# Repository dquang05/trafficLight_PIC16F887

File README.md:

# Traffic Light Controller with PIC16F887

A embedded systems project that implements a 2-road traffic light controller on **PIC16F887**, with a **Python Tkinter desktop UI** for monitoring and control over UART. The project focuses on firmware development, peripheral integration, timer-based state control, and PC-side visualization.

## Features

- PIC16F887-based traffic light controller firmware
- 3 operating modes: **AUTO**, **MANUAL**, and **FLASHING**
- UART-based communication between the microcontroller and desktop UI
- Python Tkinter interface for live traffic light visualization
- I2C LCD for mode display on the hardware side
- Button control and serial command control support

## Operating Modes

### AUTO
Runs the normal traffic cycle automatically using timer-based state transitions. The UI displays countdown values for both roads.

### MANUAL
Allows the user to manually select which road gets the green light from the desktop UI.

### FLASHING
Puts the system into a caution mode where the yellow lights blink.

## How It Works

The PIC firmware handles the traffic light state machine, button input, UART command processing, and LCD updates. A timer interrupt is used for timekeeping, while the main loop updates the current mode and periodically sends system state data to the PC.

The desktop UI connects through a serial port, sends commands, and visualizes the current traffic light states in real time.

## Controls

Supported serial/UI commands:

- `A` → AUTO
- `N` → MANUAL
- `F` → FLASHING
- `M` → NEXT MODE
- `R1` → Road 1 Go
- `R2` → Road 2 Go

## How to Use

1. Build and flash the firmware to the PIC16F887.
2. Connect the board to the PC through UART.
3. Run the Python UI.
4. Select the correct COM port and baud rate, then press **Connect**.
5. Use the UI buttons to switch modes and control the intersection.

## Wiring Notes

- `RC3` → I2C SCL
- `RC4` → I2C SDA
- `RB0`, `RB1`, `RB2` → push buttons
- UART baud rate in the current setup: **9600**

## Fault notes
- This is a small project, i do not optimal it for fault tolerance, so there are some faults in the code, such as:
  - All the components must be connected or the hardware may not function correctly.
  - If the LCD is not properly initialized or connected, it will not run correctly until the MCU is reset.

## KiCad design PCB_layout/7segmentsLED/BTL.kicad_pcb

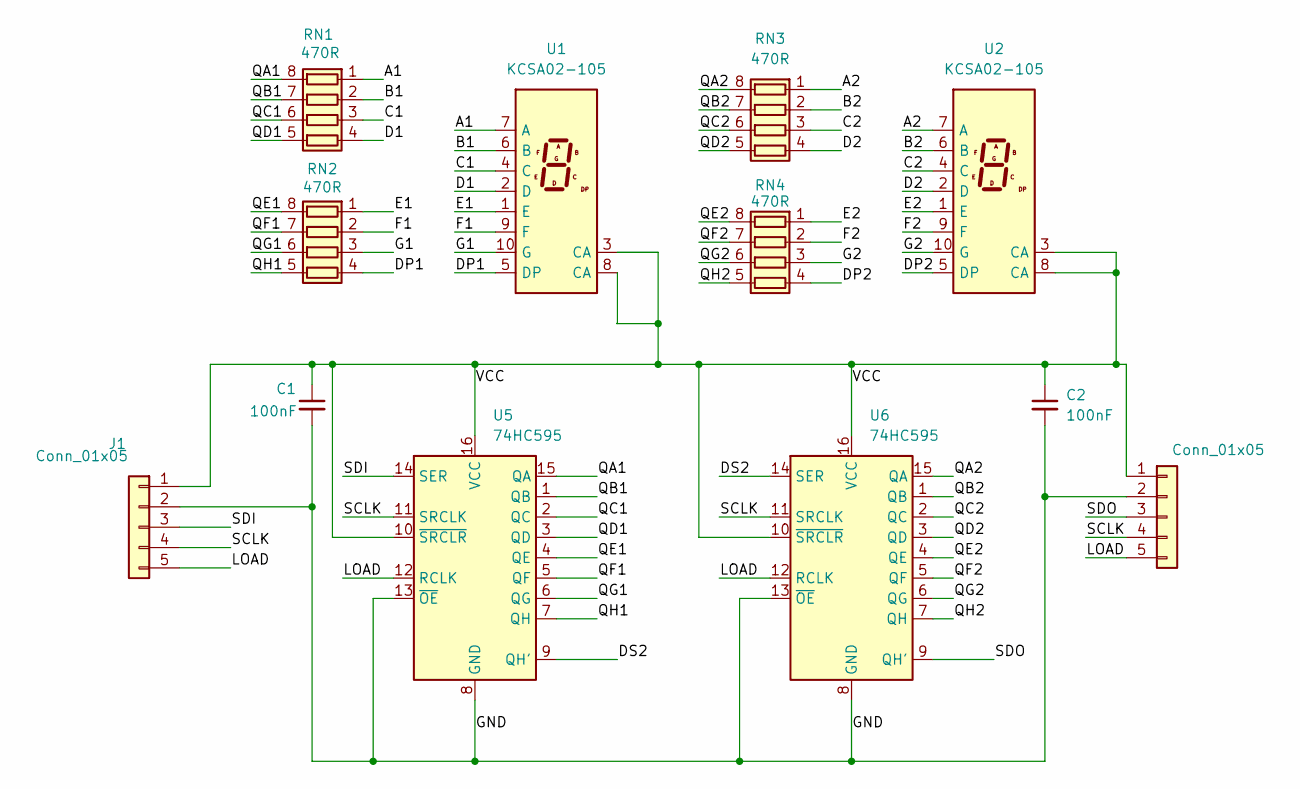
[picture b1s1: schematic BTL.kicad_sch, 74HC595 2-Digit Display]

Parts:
C1, C2: 100nF; C_0805_2012Metric
J1, J2: Conn_01x05; PinHeader_1x05_P2.54mm_Vertical
RN1, RN2, RN3, RN4: 470R; R_Array_Convex_4x0603
U1, U2: KCSA02-105; D1X8K
U5, U6: 74HC595; SOIC-16_3.9x9.9mm_P1.27mm

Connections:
/A1: RN1.1 (R1.1), U1.7 (A)
/A2: RN3.1 (R1.1), U2.7 (A)
/B1: RN1.2 (R2.1), U1.6 (B)
/B2: RN3.2 (R2.1), U2.6 (B)
/C1: RN1.3 (R3.1), U1.4 (C)
/C2: RN3.3 (R3.1), U2.4 (C)
/D1: RN1.4 (R4.1), U1.2 (D)
/D2: RN3.4 (R4.1), U2.2 (D)
/DP1: RN2.4 (R4.1), U1.5 (DP)
/DP2: RN4.4 (R4.1), U2.5 (DP)
/DS2: U5.9 (QH'), U6.14 (SER)
/E1: RN2.1 (R1.1), U1.1 (E)
/E2: RN4.1 (R1.1), U2.1 (E)
/F1: RN2.2 (R2.1), U1.9 (F)
/F2: RN4.2 (R2.1), U2.9 (F)
/G1: RN2.3 (R3.1), U1.10 (G)
/G2: RN4.3 (R3.1), U2.10 (G)
/GND: C1.2, C2.2, J1.2, J2.2, U5.8 (GND), U5.13 (~OE), U6.8 (GND), U6.13 (~OE)
/LOAD: J1.5, J2.5, U5.12 (RCLK), U6.12 (RCLK)
/QA1: RN1.8 (R1.2), U5.15 (QA)
/QA2: RN3.8 (R1.2), U6.15 (QA)
/QB1: RN1.7 (R2.2), U5.1 (QB)
/QB2: RN3.7 (R2.2), U6.1 (QB)
/QC1: RN1.6 (R3.2), U5.2 (QC)
/QC2: RN3.6 (R3.2), U6.2 (QC)
/QD1: RN1.5 (R4.2), U5.3 (QD)
/QD2: RN3.5 (R4.2), U6.3 (QD)
/QE1: RN2.8 (R1.2), U5.4 (QE)
/QE2: RN4.8 (R1.2), U6.4 (QE)
/QF1: RN2.7 (R2.2), U5.5 (QF)
/QF2: RN4.7 (R2.2), U6.5 (QF)
/QG1: RN2.6 (R3.2), U5.6 (QG)
/QG2: RN4.6 (R3.2), U6.6 (QG)
/QH1: RN2.5 (R4.2), U5.7 (QH)
/QH2: RN4.5 (R4.2), U6.7 (QH)
/SCLK: J1.4, J2.4, U5.11 (SRCLK), U6.11 (SRCLK)
/SDI: J1.3, U5.14 (SER)
/SDO: J2.3, U6.9 (QH')
/VCC: C1.1, C2.1, J1.1, J2.1, U1.3 (CA), U1.8 (CA), U2.3 (CA), U2.8 (CA), U5.10 (~SRCLR), U5.16 (VCC), U6.10 (~SRCLR), U6.16 (VCC)

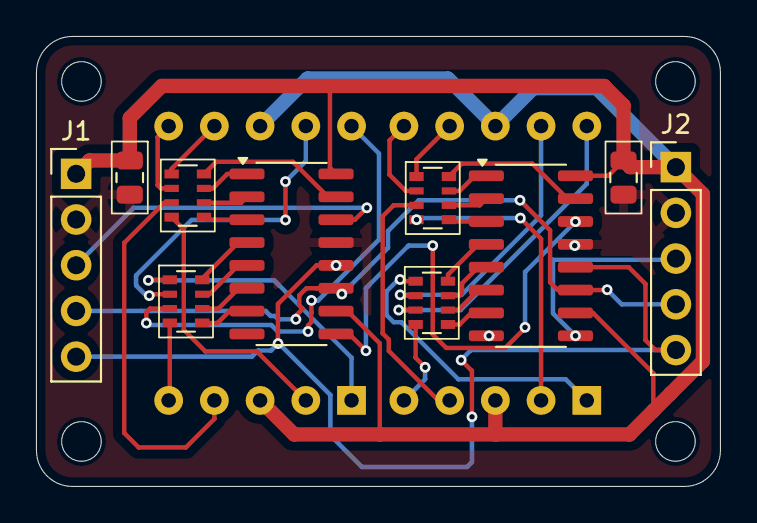
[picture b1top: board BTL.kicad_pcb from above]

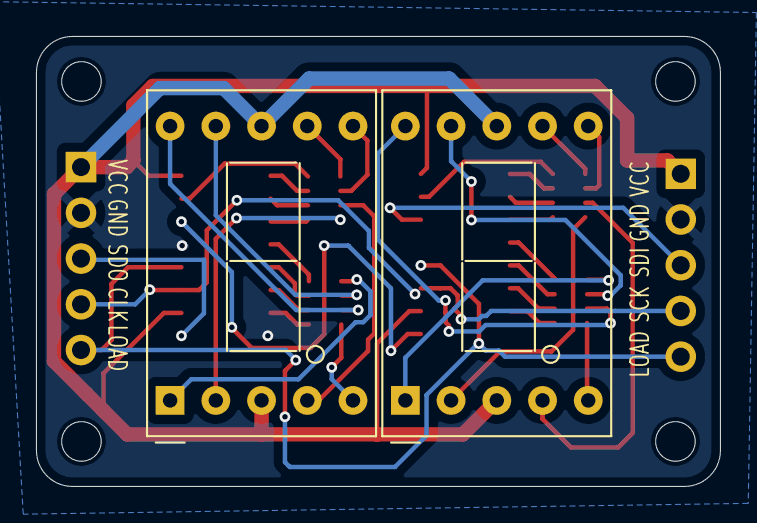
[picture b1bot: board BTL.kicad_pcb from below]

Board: 2 copper layers, 38.0 x 25.0 mm, 12 parts (2 on the bottom side), 39 nets.

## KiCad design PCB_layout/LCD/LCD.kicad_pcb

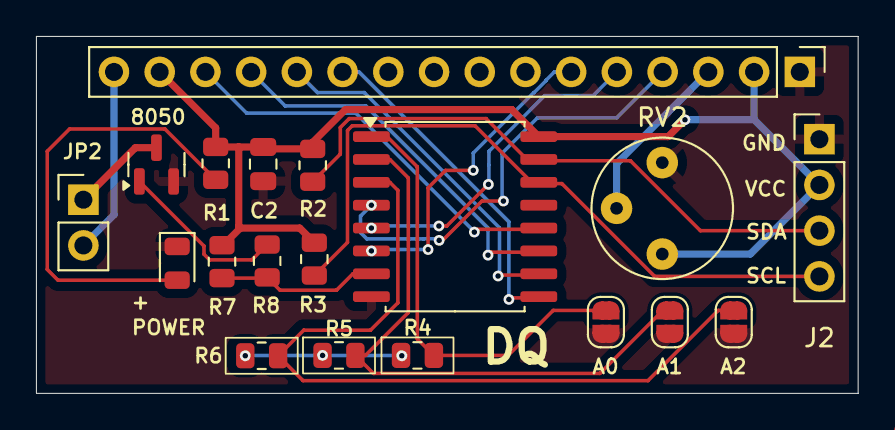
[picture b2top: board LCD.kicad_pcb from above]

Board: 2 copper layers, 45.6 x 19.8 mm, 19 parts (0 on the bottom side), 20 nets.

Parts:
8050: SS8050; SOT-23
A0, A1, A2: SolderJumper_2_Open; SolderJumper-2_P1.3mm_Open_RoundedPad1.0x1.5mm
C2: C; C_0805_2012Metric
J1: Conn_01x16; PinHeader_1x16_P2.54mm_Vertical
J2: Conn_01x04; PinHeader_1x04_P2.54mm_Vertical
JP2: Jumper_2_Bridged; PinHeader_1x02_P2.54mm_Vertical
POWER: LED; LED_0805_2012Metric
R1: 1k; R_0805_2012Metric
R1#2, R2, R2#2, R3, R3#2, R7, R8: 4k7; R_0805_2012Metric
RV2: 10k; Potentiometer_Bourns_3339P_Vertical_HandSoldering
U1: PCF8574T; SOIC-16W_7.5x10.3mm_P1.27mm

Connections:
BL: R7.2, R8.2, U1.7 (P3)
D4: J1.11, U1.9 (P4)
D5: J1.12, U1.10 (P5)
D6: J1.13, U1.11 (P6)
D7: J1.14, U1.12 (P7)
EN: J1.6, U1.6 (P2)
GND: 8050.2 (E), A0.2 (B), A1.2 (B), A2.2 (B), C2.2, J1.1, J2.1, POWER.1 (K), RV2.3, U1.8 (GND)
K: J1.16, JP2.2 (B)
unnamed: POWER.2 (A), R1.2
unnamed: 8050.3 (C), JP2.1 (A)
unnamed: A2.1 (A), R1#2.2, U1.3 (A2)
unnamed: A1.1 (A), R2.2, U1.2 (A1)
unnamed: A0.1 (A), R3.2, U1.1 (A0)
unnamed: 8050.1 (B), R8.1
RS: J1.4, U1.4 (P0)
RW: J1.5, U1.5 (P1)
SCL: J2.4, R3#2.2, U1.14 (SCL)
SDA: J2.3, R2#2.2, U1.15 (SDA)
V0: J1.3, RV2.2
VDD: C2.1, J1.2, J1.15, J2.2, R1.1, R1#2.1, R2.1, R2#2.1, R3.1, R3#2.1, R7.1, RV2.1, U1.16 (VDD)

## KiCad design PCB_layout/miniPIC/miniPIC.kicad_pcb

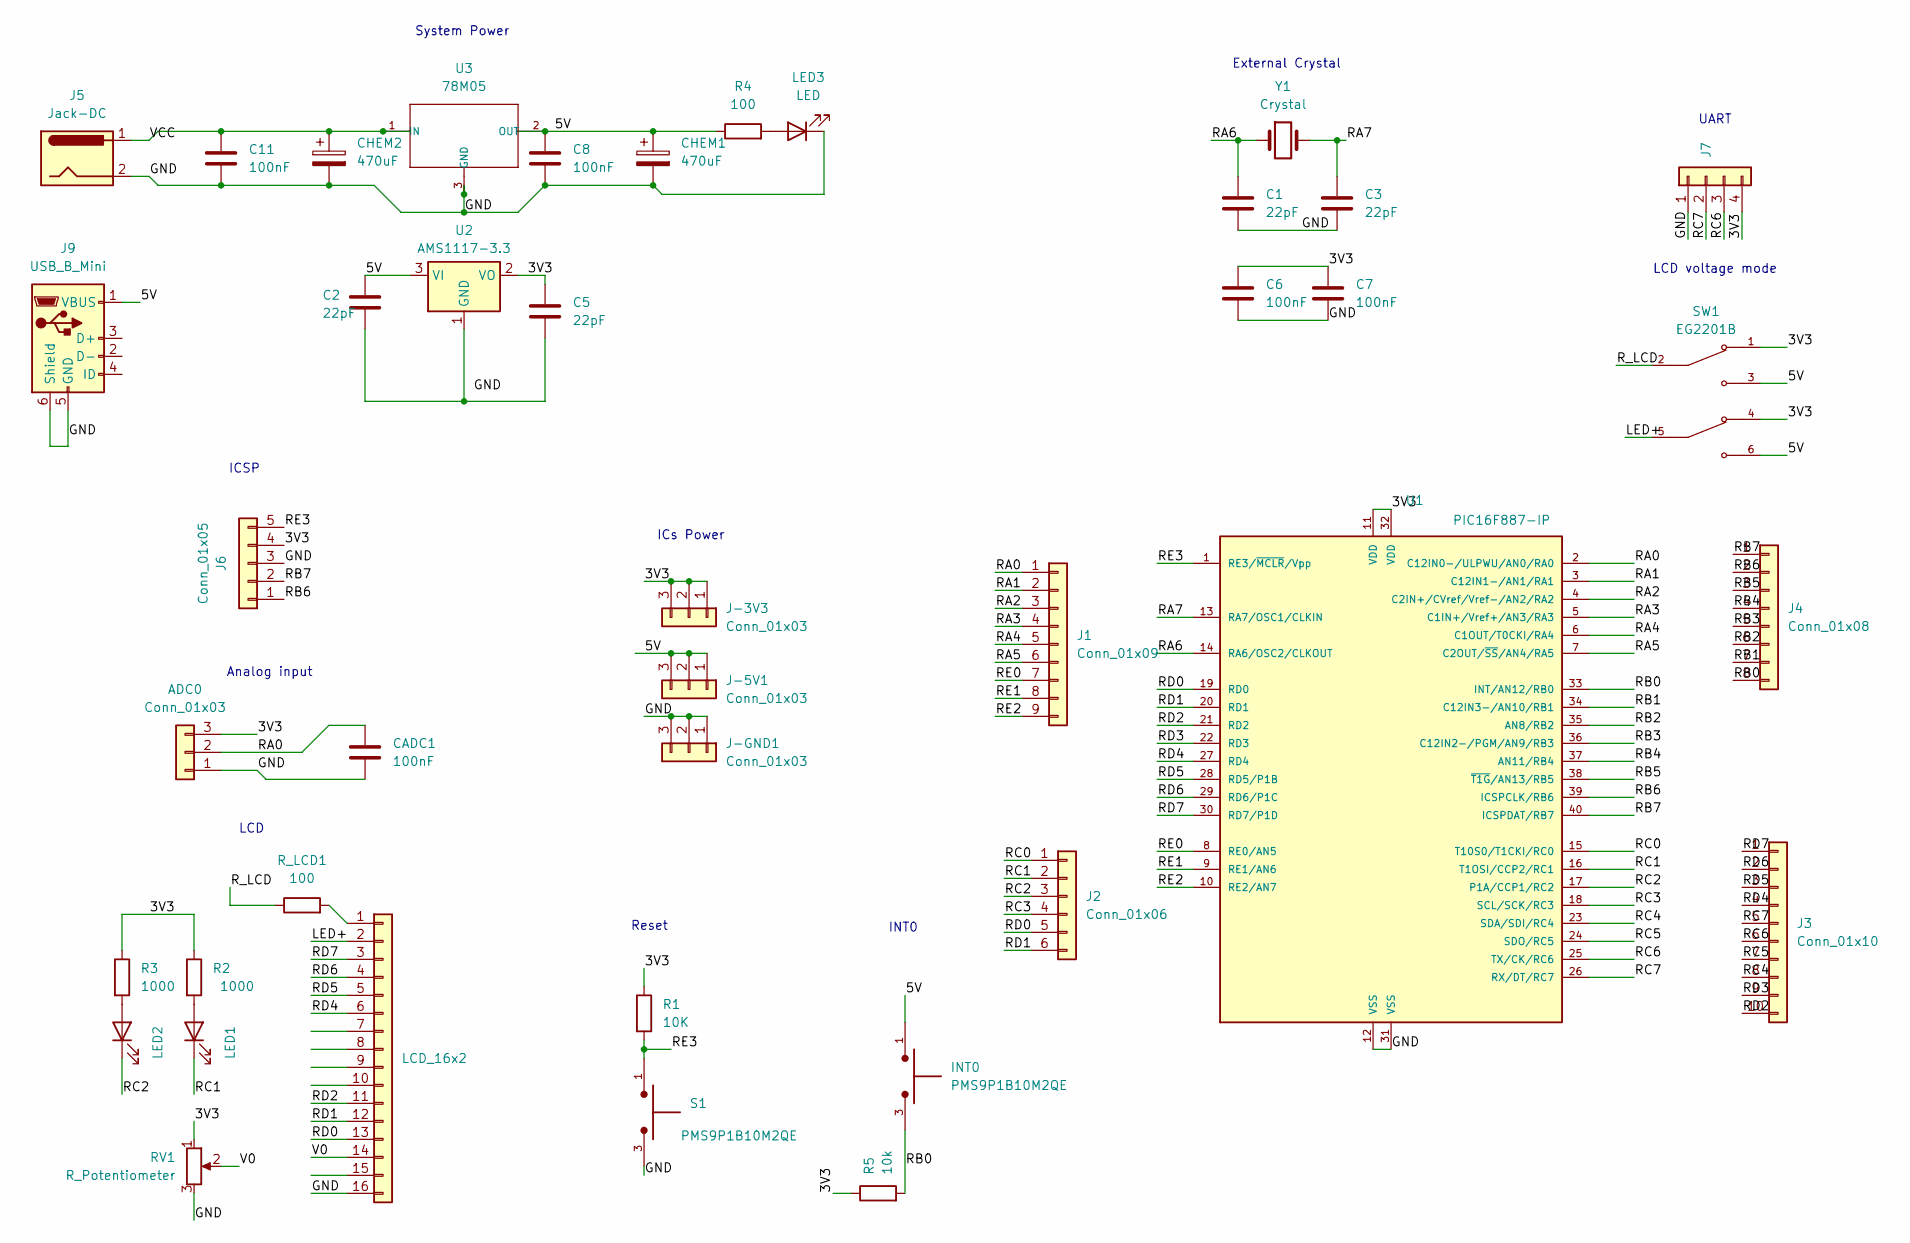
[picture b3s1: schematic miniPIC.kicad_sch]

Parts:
ADC0: Conn_01x03; PinHeader_1x03_P2.54mm_Vertical
C1, C2, C3, C5: 22pF; CP_EIA-1608-08_AVX-J
C6, C7, C8, C11: 100nF; CP_EIA-1608-08_AVX-J
CADC1: 100nF; CP_EIA-1608-08_AVX-J
CHEM1, CHEM2: 470uF; CP_Radial_D7.5mm_P2.50mm
INT0: PMS9P1B10M2QE; SW_PMS9P1B10M2QE; PARTREV A1
J1: Conn_01x09; PinHeader_1x09_P2.54mm_Vertical
J2: Conn_01x06; PinHeader_1x06_P2.54mm_Vertical
J3: Conn_01x10; PinHeader_1x10_P2.54mm_Vertical
J4: Conn_01x08; PinHeader_1x08_P2.54mm_Vertical
J5: Jack-DC; BarrelJack_Horizontal
J6: Conn_01x05; PinHeader_1x05_P2.54mm_Vertical
J7: Conn_01x04; PinSocket_1x04_P2.54mm_Vertical
J9: USB_B_Mini; USB_Mini-B_Lumberg_2486_01_Horizontal
J-3V3, J-5V1: Conn_01x03; PinHeader_1x03_P2.54mm_Vertical
J-GND1: Conn_01x03; PinHeader_1x03_P2.54mm_Vertical
LCD_16x2: Conn_01x16; PinSocket_1x16_P2.54mm_Vertical
LED1, LED2: LED; LED_0603_1608Metric_Pad1.05x0.95mm_HandSolder
LED3: LED; LED_1206_3216Metric_Pad1.42x1.75mm_HandSolder
R1: 10K; R_0805_2012Metric_Pad1.20x1.40mm_HandSolder
R2, R3: 1000; R_0805_2012Metric_Pad1.20x1.40mm_HandSolder
R4: 100; R_0805_2012Metric_Pad1.20x1.40mm_HandSolder
R5: 10k; R_0805_2012Metric_Pad1.20x1.40mm_HandSolder
RV1: R_Potentiometer; Potentiometer_Bourns_3266W_Vertical
R_LCD1: 100; R_0805_2012Metric_Pad1.20x1.40mm_HandSolder
S1: PMS9P1B10M2QE; SW_PMS9P1B10M2QE; PARTREV A1
SW1: EG2201B; SW_EG2201B; PARTREV C
U1: PIC16F887-IP; DIP1543W47P254L5175H635Q40
U2: AMS1117-3.3; SOT-223-3_TabPin2
U3: 78M05; TO-252-2
Y1: Crystal; Crystal_HC49-4H_Vertical

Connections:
/3V3: ADC0.3, C5.1, C6.1, C7.1, J6.4, J7.4, J-3V3.1, J-3V3.2, J-3V3.3, R1.1, R2.1, R3.1, R5.1, RV1.1, SW1.1, SW1.4, U1.11 (VDD), U1.32 (VDD), U2.2 (VO)
/5V: C2.1, C8.1, CHEM1.1, INT0.1, J9.1 (VBUS), J-5V1.1, J-5V1.2, J-5V1.3, R4.1, SW1.3, SW1.6, U2.3 (VI), U3.2 (OUT)
/LED+: LCD_16x2.2, SW1.5
/RA0: ADC0.2, CADC1.1, J1.1, U1.2 (C12IN0-/ULPWU/AN0/RA0)
/RA1: J1.2, U1.3 (C12IN1-/AN1/RA1)
/RA2: J1.3, U1.4 (C2IN+/CVref/Vref-/AN2/RA2)
/RA3: J1.4, U1.5 (C1IN+/Vref+/AN3/RA3)
/RA4: J1.5, U1.6 (C1OUT/T0CKI/RA4)
/RA5: J1.6, U1.7 (C2OUT/~SS/AN4/RA5)
/RA6: C1.1, U1.14 (RA6/OSC2/CLKOUT), Y1.1
/RA7: C3.1, U1.13 (RA7/OSC1/CLKIN), Y1.2
/RB0: INT0.3, J4.8, R5.2, U1.33 (INT/AN12/RB0)
/RB1: J4.7, U1.34 (C12IN3-/AN10/RB1)
/RB2: J4.6, U1.35 (AN8/RB2)
/RB3: J4.5, U1.36 (C12IN2-/PGM/AN9/RB3)
/RB4: J4.4, U1.37 (AN11/RB4)
/RB5: J4.3, U1.38 (~T1G/AN13/RB5)
/RB6: J4.2, J6.1, U1.39 (ICSPCLK/RB6)
/RB7: J4.1, J6.2, U1.40 (ICSPDAT/RB7)
/RC0: J2.1, U1.15 (T10S0/T1CKI/RC0)
/RC1: J2.2, LED1.1 (K), U1.16 (T1OSI/CCP2/RC1)
/RC2: J2.3, LED2.1 (K), U1.17 (P1A/CCP1/RC2)
/RC3: J2.4, U1.18 (SCL/SCK/RC3)
/RC4: J3.8, U1.23 (SDA/SDI/RC4)
/RC5: J3.7, U1.24 (SDO/RC5)
/RC6: J3.6, J7.3, U1.25 (TX/CK/RC6)
/RC7: J3.5, J7.2, U1.26 (RX/DT/RC7)
/RD0: J2.5, LCD_16x2.13, U1.19 (RD0)
/RD1: J2.6, LCD_16x2.12, U1.20 (RD1)
/RD2: J3.10, LCD_16x2.11, U1.21 (RD2)
/RD3: J3.9, U1.22 (RD3)
/RD4: J3.4, LCD_16x2.6, U1.27 (RD4)
/RD5: J3.3, LCD_16x2.5, U1.28 (RD5/P1B)
/RD6: J3.2, LCD_16x2.4, U1.29 (RD6/P1C)
/RD7: J3.1, LCD_16x2.3, U1.30 (RD7/P1D)
/RE0: J1.7, U1.8 (RE0/AN5)
/RE1: J1.8, U1.9 (RE1/AN6)
/RE2: J1.9, U1.10 (RE2/AN7)
/RE3: J6.5, R1.2, S1.1, U1.1 (RE3/~MCLR/Vpp)
/R_LCD: R_LCD1.1, SW1.2
/V0: LCD_16x2.14, RV1.2
/VCC: C11.1, CHEM2.1, J5.1, U3.1 (IN)
unnamed: LCD_16x2.1, R_LCD1.2
unnamed: LED1.2 (A), R2.2
unnamed: LED2.2 (A), R3.2
unnamed: LED3.2 (A), R4.2

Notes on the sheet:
External Crystal
LCD
Reset
UART
System Power
INT0
LCD voltage mode
ICSP
ICs Power
Analog input

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
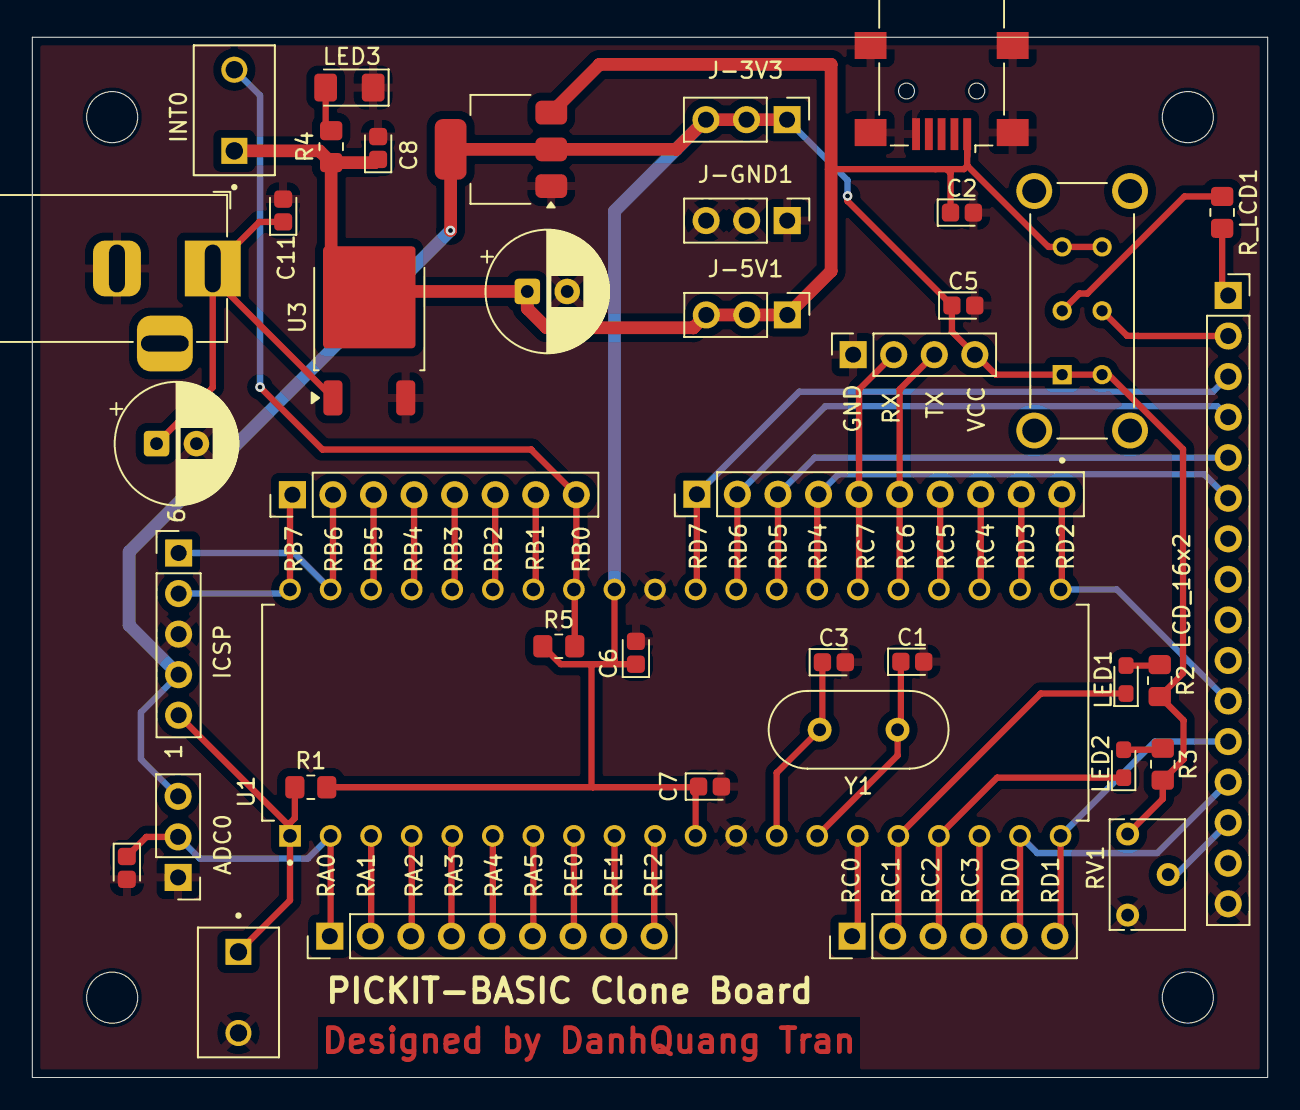
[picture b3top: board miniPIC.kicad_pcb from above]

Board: 2 copper layers, 77.4 x 65.2 mm, 41 parts (0 on the bottom side), 47 nets.

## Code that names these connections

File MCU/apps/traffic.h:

#ifndef TRAFFIC_H
#define TRAFFIC_H

#include <stdint.h>
#include <xc.h> 

// Các thông số thời gian
#define GREEN1_TIME   15
#define GREEN2_TIME   15
#define YELLOW_TIME  3

// Định nghĩa chân đèn giao thông
#define GREEN1   RA0  
#define YELLOW1  RA1  
#define RED1     RA2         
#define GREEN2   RA3  
#define YELLOW2  RA4    
#define RED2     RA5     

// Các biến toàn cục
extern volatile uint16_t timer_counter;
extern volatile uint8_t system_state;
extern volatile uint8_t exitsign;
extern volatile uint8_t mode;
extern volatile uint8_t countdown_NS; 
extern volatile uint8_t countdown_EW; 
extern volatile uint8_t road1_flag;
extern volatile uint8_t road2_flag;

// Các hàm điều khiển đèn
void Auto_Mode_Timer(void);
void Midnight_Mode_Timer(void);
void Manual_Mode(void);
void Opposite_State(void);
void Display_Countdown(uint8_t countdown_EW, uint8_t countdown_NS);
void ShiftOut_1Byte(uint8_t data);
void Clear_Display(void);

#endif

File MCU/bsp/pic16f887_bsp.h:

#include <xc.h> // include processor files - each processor file is guarded.  

// CONFIG1
#pragma config FOSC = INTRC_NOCLKOUT        // Oscillator Selection bits (RC oscillator: CLKOUT function on RA6/OSC2/CLKOUT pin, RC on RA7/OSC1/CLKIN)
#pragma config WDTE = OFF       // Watchdog Timer Enable bit (WDT disabled and can be enabled by SWDTEN bit of the WDTCON register)

#pragma config CP = OFF         // Code Protection bit (Program memory code protection is disabled)
#pragma config CPD = OFF        // Data Code Protection bit (Data memory code protection is disabled)
#pragma config BOREN = ON       // Brown Out Reset Selection bits (BOR enabled)
#pragma config IESO = OFF       // Internal External Switchover bit (Internal/External Switchover mode is disabled)
#pragma config FCMEN = OFF      // Fail-Safe Clock Monitor Enabled bit (Fail-Safe Clock Monitor is disabled)
#pragma config LVP = OFF        // Low Voltage Programming Enable bit (RB3 pin has digital I/O, HV on MCLR must be used for programming)

// CONFIG2
#pragma config BOR4V = BOR40V   // Brown-out Reset Selection bit (Brown-out Reset set to 4.0V)
#pragma config WRT = OFF        // Flash Program Memory Self Write Enable bits (Write protection off)

// #pragma config statements should precede project file includes.
// Use project enums instead of #define for ON and OFF.

#define _XTAL_FREQ 4000000 // Set the clock frequency to 4MHz

#pragma config PWRTE = ON       // Power-up Timer Enable bit (PWRT enabled)
#pragma config MCLRE = ON       // RE3/MCLR pin function select bit (RE3/MCLR pin function is digital input, MCLR internally tied to VDD)

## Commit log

2026-03-23 first commit to save class project
2026-03-23 add readme and gitignore
2026-03-23 add proteus simulation
2026-04-19 fix: ignore unecessary files
2026-04-19 Stop tracking editor/build artifacts; update .gitignore
2026-04-23 add: two physical button to change mode on lane
2026-04-23 fix: 2 button conditions
2026-04-23 Remove _build from tracking
2026-04-25 Ignore generated CMake files
2026-04-25 fix: ignore cmake generated files
2026-05-10 add: PCB_layout
